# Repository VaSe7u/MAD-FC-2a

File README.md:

**MAD-FC-2a** quadrocopter flight controller.

This is a project of a flight controller for quadcopter. The [main source file][cpp] is designed to be descriptive of a multirotor flight controller algorithm. It is a concrete implementation that uses ATmega328P, MPU9255 and nRF24L01+ hardware but they can be easily replaced. The schematic and board layout for the flight controller and the remote board can be found in their respective circuit folders. The project depends on [MAD][madLink] library which is a common library for the flight controller and the remote.

*Not tested, Old project: [FC-alpha2][fcAlpha2].*

Flight Controller
=================
Schematic:
----------

Board:
----------

.jpg)

Photo:
----------

Remote
======
Schematic:
----------

Board:
----------

License
=======
The MIT License (MIT)

Copyright (c) 2016 Vasil Kalchev

Permission is hereby granted, free of charge, to any person obtaining a copy
of this software and associated documentation files (the "Software"), to deal
in the Software without restriction, including without limitation the rights
to use, copy, modify, merge, publish, distribute, sublicense, and/or sell
copies of the Software, and to permit persons to whom the Software is
furnished to do so, subject to the following conditions:

The above copyright notice and this permission notice shall be included in all
copies or substantial portions of the Software.

THE SOFTWARE IS PROVIDED "AS IS", WITHOUT WARRANTY OF ANY KIND, EXPRESS OR
IMPLIED, INCLUDING BUT NOT LIMITED TO THE WARRANTIES OF MERCHANTABILITY,
FITNESS FOR A PARTICULAR PURPOSE AND NONINFRINGEMENT. IN NO EVENT SHALL THE
AUTHORS OR COPYRIGHT HOLDERS BE LIABLE FOR ANY CLAIM, DAMAGES OR OTHER
LIABILITY, WHETHER IN AN ACTION OF CONTRACT, TORT OR OTHERWISE, ARISING FROM,
OUT OF OR IN CONNECTION WITH THE SOFTWARE OR THE USE OR OTHER DEALINGS IN THE
SOFTWARE.

[cpp]: https://github.com/VaSe7u/MAD-FC-2a/blob/master/code/MAD-FC-2a.ino
[madLink]: https://github.com/VaSe7u/MAD
[fcAlpha2]: https://github.com/VaSe7u/FC-alpha2

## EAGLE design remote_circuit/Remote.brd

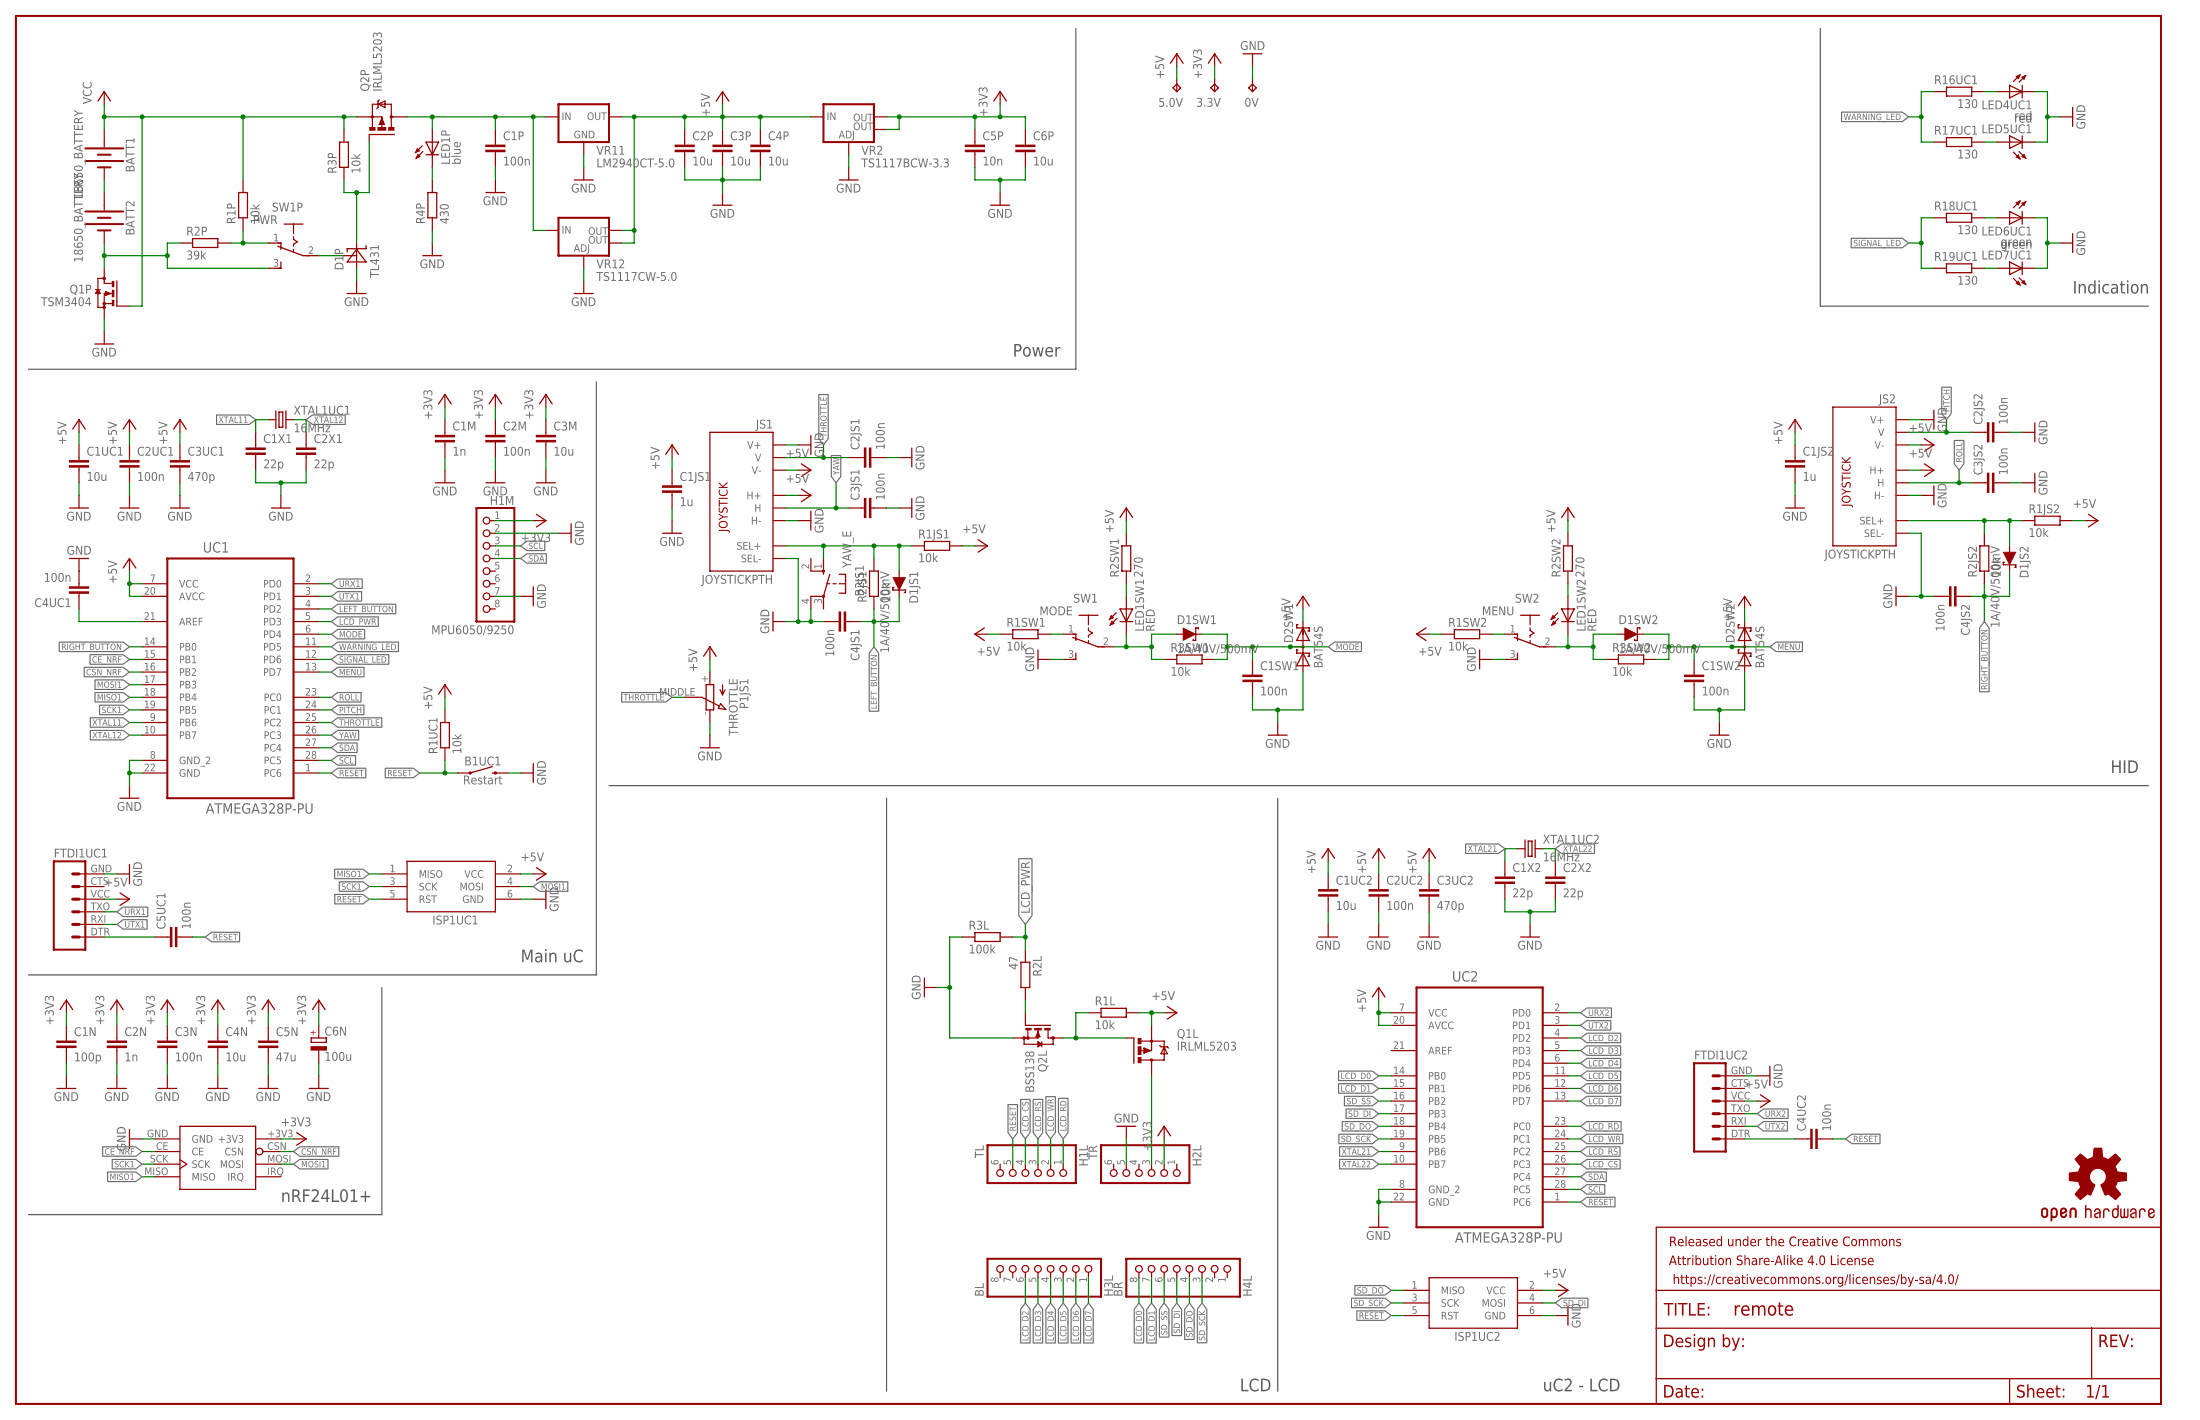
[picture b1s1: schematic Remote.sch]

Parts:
0V, 3.3V, 5.0V: TPTP10SQ; TP10SQ
B1: nRF24L01+; NRF24L01+_PA_LNA
B1UC1: Restart; TACTILE_SWITCH_SMD_6.0X3.5MM
B2JS1: YAW_E; B3F-40XX
BATT1, BATT2: 18650_BATTERY; BATTERY_HOLDER_18650
C1JS1, C1JS2: 1u; C1206
C1M, C2N: 1n; C1206
C1N: 100p; C1206
C1P, C1SW1, C1SW2, C2JS1, C2JS2, C2M, C2UC1, C2UC2, C3JS1, C3JS2, C3N, C4JS1, C4JS2, C4UC1, C4UC2, C5UC1: 100n; C1206
C1UC1, C1UC2, C2P, C3M, C3P, C4N, C4P, C6P: 10u; C1206
C1X1, C1X2, C2X1, C2X2: 22p; C1206
C3UC1, C3UC2: 470p; C1206
C5N: 47u; C3225
C5P: 10n; C1206
C6N: 100u; 153CLV-0505
D1JS1, D1JS2, D1SW1, D1SW2: 1A/40V/500mV; SMA-DIODE
D1P: TL431; SO-8
D2SW1, D2SW2: BAT54S; SOT23
FRAME2: FRAME-LEDGER; CREATIVE_COMMONS
FTDI1UC1, FTDI1UC2: FTDI_BASICPTH; FTDI_BASIC
H1L: TL; 1X06
H1M: MPU6050/9250; 1X08
H2L: TR; 1X06
H3L: BL; 1X08
H4L: BR; 1X08
ISP1UC1, ISP1UC2: AVRISP-6; AVRISP
JS1, JS2: JOYSTICKPTH; JOYSTICK
LED1P: blue; SML1206
LED1SW1, LED1SW2: RED; SML1206
LED4UC1: red; SML1206
LED5UC1: red; 1206
LED6UC1: green; SML1206
LED7UC1: green; 1206
LOGO1: OSHW-LOGOL-COPPER; OSHW-LOGO-L_COPPER
P1JS1: THROTTLE; SLIDE_POTENTIOMETER
Q1L, Q2P: IRLML5203; MICRO3
Q1P: TSM3404; SOT23
Q2L: BSS138; SOT23
R1JS1, R1JS2, R1L, R1P, R1SW1, R1SW2, R1UC1, R2JS1, R2JS2, R3P, R3SW1, R3SW2: 10k; R1206
R2L: 47; R1206
R2P: 39k; R1206
R2SW1, R2SW2: 270; R1206
R3L: 100k; R1206
R4P: 430; R1206
R16UC1, R17UC1, R18UC1, R19UC1: 130; R1206
SW1: MODE; SWITCH_2MM
SW1P: PWR; SWITCH_2MM
SW2: MENU; SWITCH_2MM
UC1, UC2: ATMEGA328P-PU; DIP254P762X457-28
VR2: TS1117BCW-3.3; SOT223
VR11: LM2940CT-5.0; 78XXL
VR12: TS1117CW-5.0; SOT223
XTAL1UC1, XTAL1UC2: 16MHz; HC49/S

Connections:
+3V3: 3.3V.TP, B1.+3V3, C1M.1, C1N.1, C2M.1, C2N.1, C3M.1, C3N.1, C4N.1, C5N.1, C5P.1, C6N.+, C6P.1, H1M.1, H2L.2, VR2.2 (OUT), VR2.4 (OUT)
+5V: 5.0V.TP, C1JS1.1, C1JS2.1, C1UC1.1, C1UC2.1, C2P.1, C2UC1.1, C2UC2.1, C3P.1, C3UC1.1, C3UC2.1, C4P.1, D2SW1.2 (C2), D2SW2.2 (C2), FTDI1UC1.VCC (4), FTDI1UC2.VCC (4), ISP1UC1.2 (VCC), ISP1UC2.2 (VCC), JS1.H1 (H+), JS1.V3 (V-), JS2.H1 (H+), JS2.V3 (V-), P1JS1.+, Q1L.2 (S), R1JS1.2, R1JS2.2, R1L.2, R1SW1.1, R1SW2.1, R1UC1.2, R2SW1.2, R2SW2.2, UC1.7 (VCC), UC1.20 (AVCC), UC2.7 (VCC), UC2.20 (AVCC), VR2.3 (IN), VR11.OUT, VR12.2 (OUT), VR12.4 (OUT)
CE_NRF: B1.CE, UC1.15 (PB1)
CSN_NRF: B1.CSN, UC1.16 (PB2)
GND: 0V.TP, B1.GND, B1UC1.2, B2JS1.4 (P1), C1JS1.2, C1JS2.2, C1M.2, C1N.2, C1P.2, C1SW1.2, C1SW2.2, C1UC1.2, C1UC2.2, C1X1.2, C1X2.2, C2JS1.2, C2JS2.2, C2M.2, C2N.2, C2P.2, C2UC1.2, C2UC2.2, C2X1.2, C2X2.2, C3JS1.2, C3JS2.2, C3M.2, C3N.2, C3P.2, C3UC1.2, C3UC2.2, C4JS1.2, C4JS2.2, C4N.2, C4P.2, C4UC1.2, C5N.2, C5P.2, C6N.-, C6P.2, D1P.2 (ANODE), D1P.3 (ANODE), D1P.6 (ANODE), D1P.7 (ANODE), D2SW1.1 (A1), D2SW2.1 (A1), FTDI1UC1.GND (6), FTDI1UC2.GND (6), H1M.2, H1M.7, H2L.5, ISP1UC1.6 (GND), ISP1UC2.6 (GND), JS1.B2A (SEL-), JS1.H3 (H-), JS1.V1 (V+), JS2.B2A (SEL-), JS2.H3 (H-), JS2.V1 (V+), LED4UC1.C, LED5UC1.C, LED6UC1.C, LED7UC1.C, P1JS1.-, Q1P.2 (S), Q2L.2 (S), R3L.1, R4P.1, SW1.3, SW2.3, UC1.8 (GND_2), UC1.22 (GND), UC2.8 (GND_2), UC2.22 (GND), VR2.1 (ADJ), VR11.GND, VR12.1 (ADJ)
LCD_CS: H1L.4, UC2.26 (PC3)
LCD_D0: H4L.8, UC2.14 (PB0)
LCD_D1: H4L.7, UC2.15 (PB1)
LCD_D2: H3L.6, UC2.4 (PD2)
LCD_D3: H3L.5, UC2.5 (PD3)
LCD_D4: H3L.4, UC2.6 (PD4)
LCD_D5: H3L.3, UC2.11 (PD5)
LCD_D6: H3L.2, UC2.12 (PD6)
LCD_D7: H3L.1, UC2.13 (PD7)
LCD_PWR: R2L.1, R3L.2, UC1.5 (PD3)
LCD_RD: H1L.1, UC2.23 (PC0)
LCD_RS: H1L.3, UC2.25 (PC2)
LCD_WR: H1L.2, UC2.24 (PC1)
LEFT_BUTTON: C4JS1.1, D1JS1.C, R2JS1.1, UC1.4 (PD2)
MENU: C1SW2.1, D1SW2.C, D2SW2.3 (C1A2), R3SW2.2, UC1.13 (PD7)
MISO1: B1.MISO, ISP1UC1.1 (MISO), UC1.18 (PB4)
MODE: C1SW1.1, D1SW1.C, D2SW1.3 (C1A2), R3SW1.2, UC1.6 (PD4)
MOSI1: B1.MOSI, ISP1UC1.4 (MOSI), UC1.17 (PB3)
unnamed: C4UC1.1, UC1.21 (AREF)
unnamed: LED1SW1.A, R2SW1.1
unnamed: C5UC1.1, FTDI1UC1.DTR (1)
unnamed: BATT1.-, BATT2.+
unnamed: R1SW2.2, SW2.1
unnamed: D1SW2.A, LED1SW2.C, R3SW2.1, SW2.2
unnamed: LED1P.C, R4P.2
unnamed: D1SW1.A, LED1SW1.C, R3SW1.1, SW1.2
unnamed: LED1SW2.A, R2SW2.1
unnamed: R1SW1.2, SW1.1
unnamed: D1JS2.A, JS2.B1A (SEL+), R1JS2.1, R2JS2.2
unnamed: BATT2.-, Q1P.3 (D), R2P.1, SW1P.3
unnamed: LED4UC1.A, R16UC1.1
unnamed: LED6UC1.A, R18UC1.1
unnamed: C4UC2.1, FTDI1UC2.DTR (1)
unnamed: LED5UC1.A, R17UC1.1
unnamed: H2L.3, Q1L.3 (D)
unnamed: LED7UC1.A, R19UC1.1
unnamed: C1P.1, LED1P.A, Q2P.3 (D), VR11.IN, VR12.3 (IN)
unnamed: D1P.8 (REFERENCE), SW1P.2
unnamed: R1P.1, R2P.2, SW1P.1
unnamed: Q1L.1 (G), Q2L.3 (D), R1L.1
unnamed: D1P.1 (CATHODE), Q2P.1 (G), R3P.1
unnamed: Q2L.1 (G), R2L.2
PITCH: C2JS2.1, JS2.V2 (V), UC1.24 (PC1)
RESET: B1UC1.1, C4UC2.2, C5UC1.2, H1L.5, ISP1UC1.5 (RST), ISP1UC2.5 (RST), R1UC1.1, UC1.1 (PC6), UC2.1 (PC6)
RIGHT_BUTTON: C4JS2.1, D1JS2.C, R2JS2.1, UC1.14 (PB0)
ROLL: C3JS2.1, JS2.H2 (H), UC1.23 (PC0)
SCK1: B1.SCK, ISP1UC1.3 (SCK), UC1.19 (PB5)
SCL: H1M.3, UC1.28 (PC5), UC2.28 (PC5)
SDA: H1M.4, UC1.27 (PC4), UC2.27 (PC4)
SD_DI: H4L.5, ISP1UC2.4 (MOSI), UC2.17 (PB3)
SD_DO: H4L.4, ISP1UC2.1 (MISO), UC2.18 (PB4)
SD_SCK: H4L.3, ISP1UC2.3 (SCK), UC2.19 (PB5)
SD_SS: H4L.6, UC2.16 (PB2)
SIGNAL_LED: R18UC1.2, R19UC1.2, UC1.12 (PD6)
SN1: B2JS1.1 (S), D1JS1.A, JS1.B1A (SEL+), R1JS1.1, R2JS1.2
THROTTLE: C2JS1.1, JS1.V2 (V), P1JS1.MIDDLE, UC1.25 (PC2)
URX1: FTDI1UC1.TXO (3), UC1.2 (PD0)
URX2: FTDI1UC2.TXO (3), UC2.2 (PD0)
UTX1: FTDI1UC1.RXI (2), UC1.3 (PD1)
UTX2: FTDI1UC2.RXI (2), UC2.3 (PD1)
VCC: BATT1.+, Q1P.1 (G), Q2P.2 (S), R1P.2, R3P.2
WARNING_LED: R16UC1.2, R17UC1.2, UC1.11 (PD5)
XTAL11: C1X1.1, UC1.9 (PB6), XTAL1UC1.1
XTAL12: C2X1.1, UC1.10 (PB7), XTAL1UC1.2
XTAL21: C1X2.1, UC2.9 (PB6), XTAL1UC2.1
XTAL22: C2X2.1, UC2.10 (PB7), XTAL1UC2.2
YAW: C3JS1.1, JS1.H2 (H), UC1.26 (PC3)

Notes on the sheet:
Power
nRF24L01+
LCD
uC2 - LCD
HID
Indication
Main uC

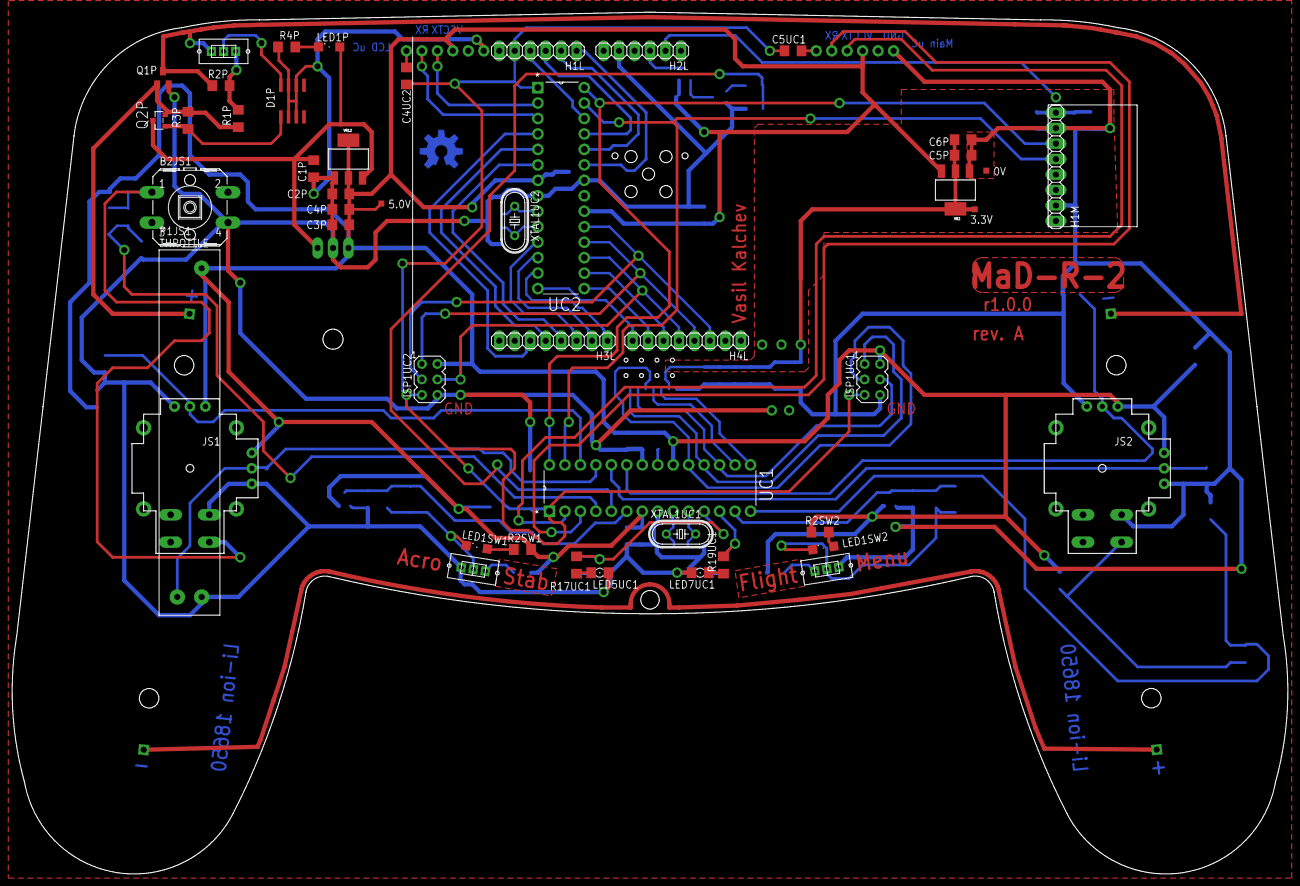
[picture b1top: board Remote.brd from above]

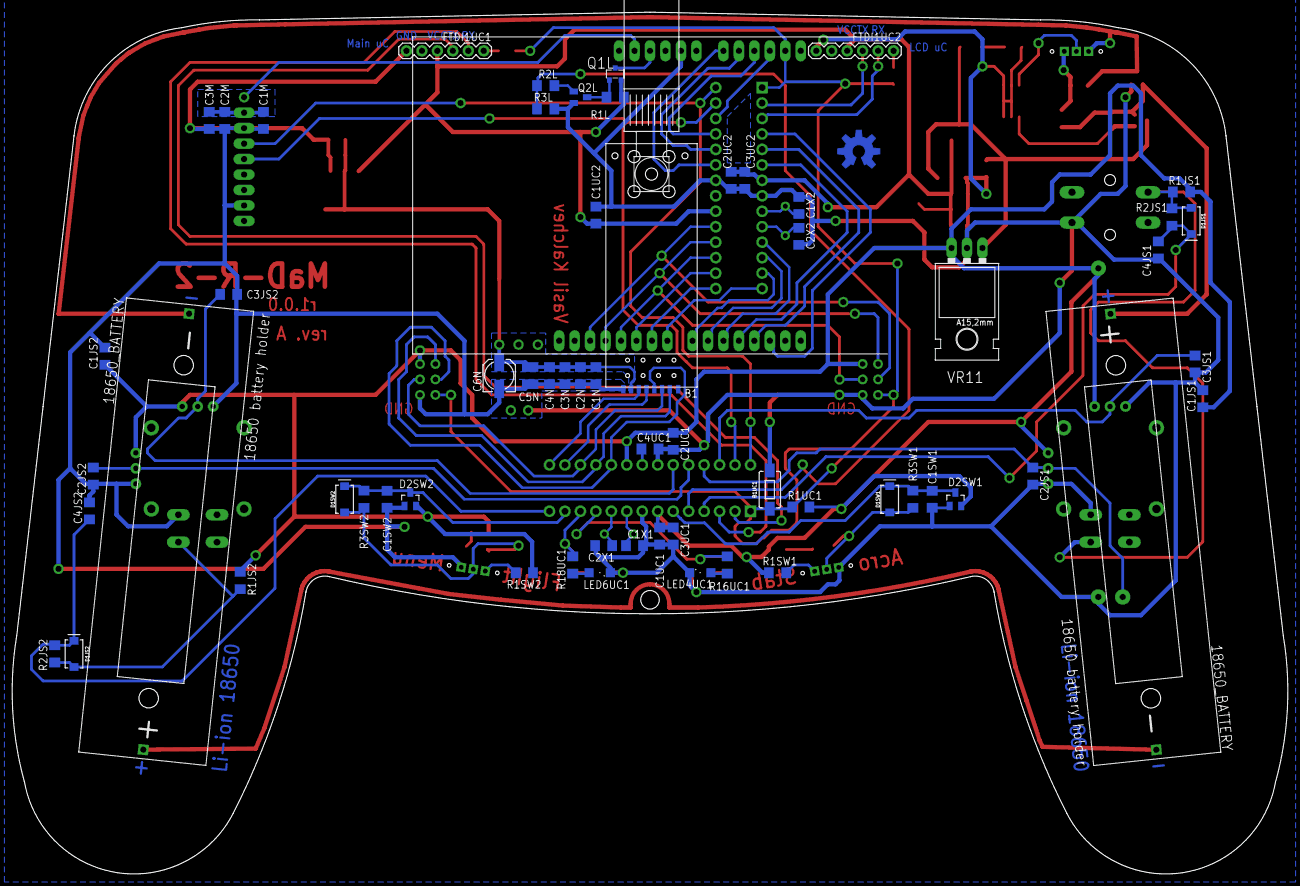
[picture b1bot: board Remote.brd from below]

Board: 2 copper layers, 209.5 x 141.5 mm, 110 parts (62 on the bottom side), 72 nets.

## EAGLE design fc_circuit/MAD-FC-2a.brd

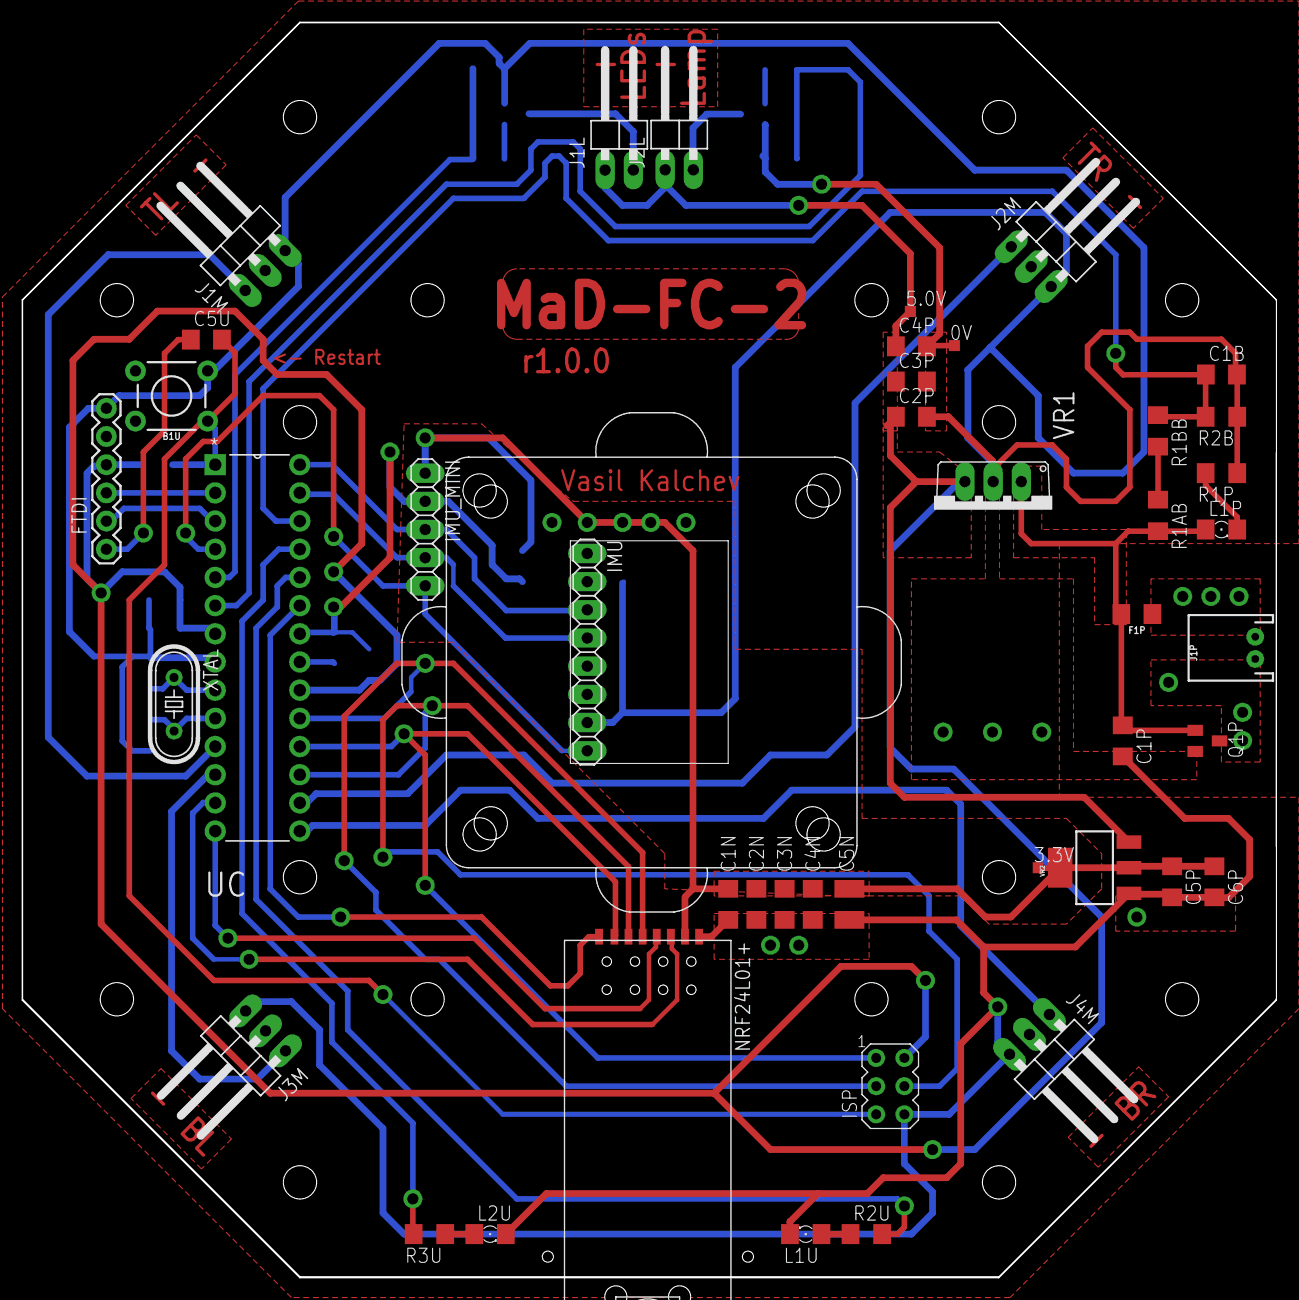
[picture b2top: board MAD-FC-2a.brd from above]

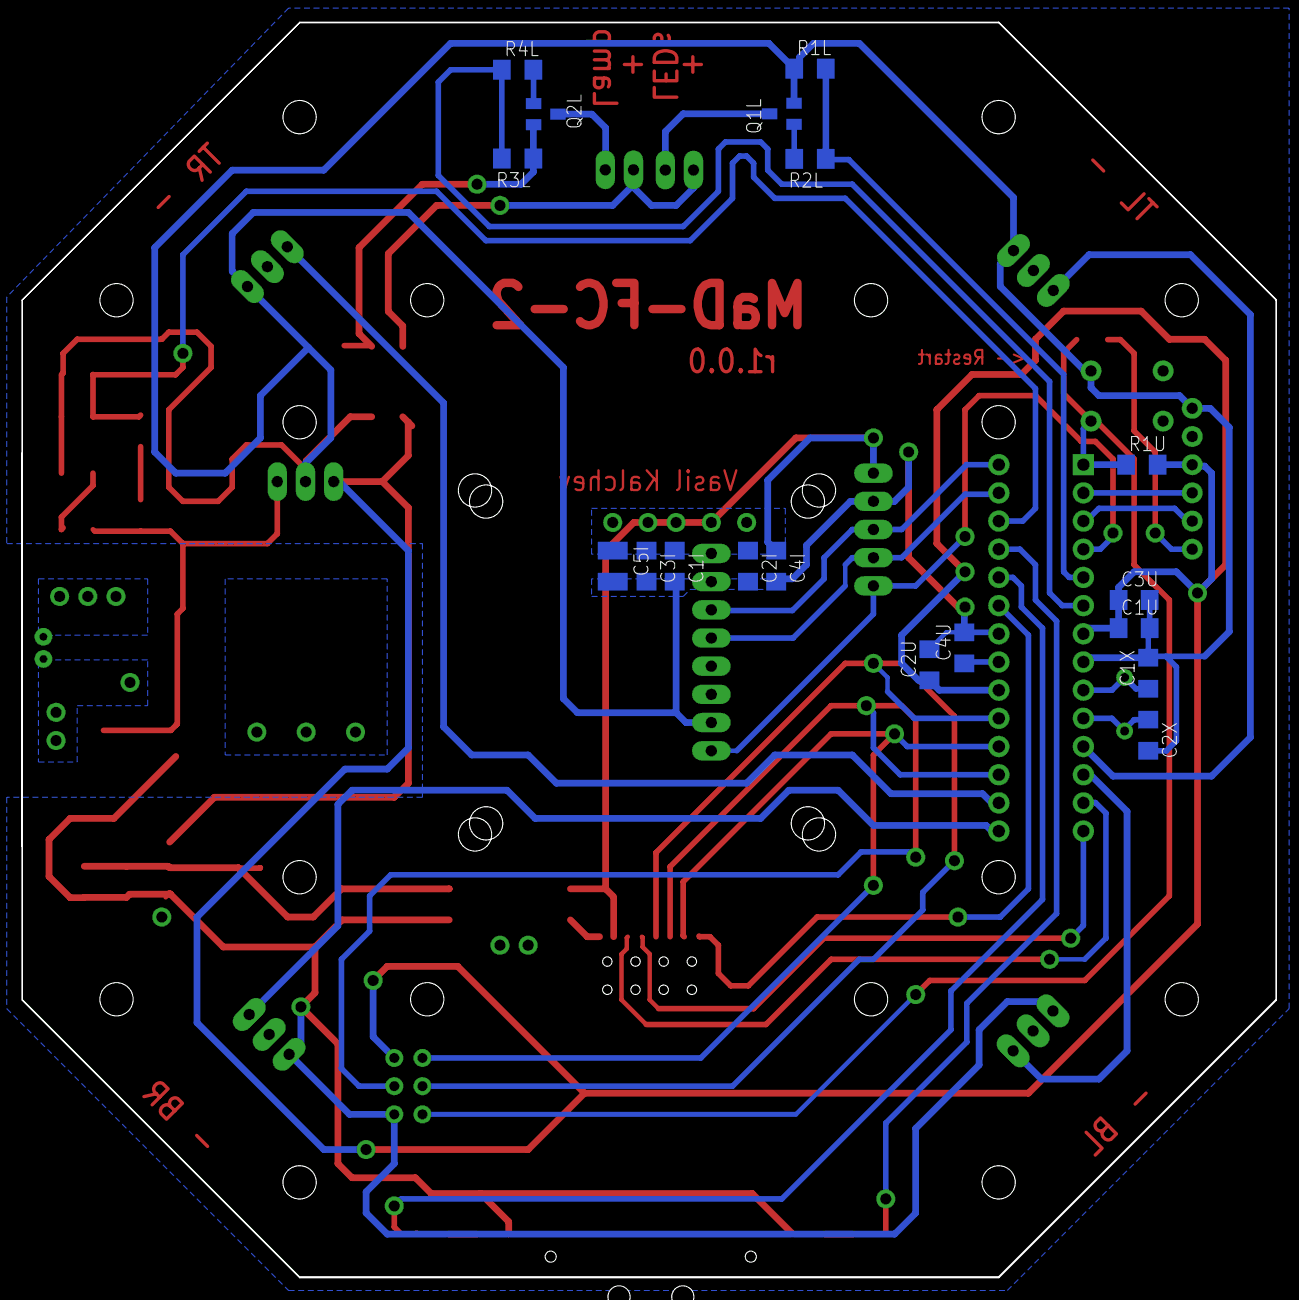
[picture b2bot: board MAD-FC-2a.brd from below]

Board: 2 copper layers, 113.0 x 113.2 mm, 64 parts (18 on the bottom side), 39 nets.

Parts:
0V, 3.3V, 5.0V: TPTP10SQ; TP10SQ
B1U: Restart; TACTILE_SWITCH_PTH_6.0MM
C1B, C1U, C2P, C3P, C4I, C4N, C4P, C6P: 10u; C1206
C1I, C1N: 100p; C1206
C1P, C2U, C3I, C3N, C4U, C5U: 100n; C1206
C1X, C2X: 22p; C1206
C2I, C2N: 1n; C1206
C3U: 470p; C1206
C5I, C5N: 100u_6.3x5.3; C3225
C5P: 10n; C1206
F1P: 2A; 1206
FTDI: FTDI_BASIC
IMU: MPU6050/9250; 1X08
IMU_MINI: MPU6050/9250; 1X05
ISP: AVRISP-6; AVRISP
J1L, J2L: 1X02/90
J1M: TL; 1X03/90
J1P: LiPo; JST-2-PTH
J2M: TR; 1X03/90
J3M: BL; 1X03/90
J4M: BR; 1X03/90
L1P: blue; 1206
L1U: red; 1206
L2U: green; 1206
NRF24L01+: nRF24L01+; NRF24L01+_PA_LNA_SMD
Q1L, Q1P, Q2L: TSM3404; SOT23
R1AB: 110k; R1206
R1BB: 20k; R1206
R1L, R3L: 100k; R1206
R1P: 680; R1206
R1U: 10k; R1206
R2B: 9k1; R1206
R2L, R4L: 33; R1206
R2U, R3U: 130; R1206
U$2: F450_TOP_PLATE
U$3: ANTI-VIBRATION_PLATE
UC: ATMEGA328P-PU; DIP254P762X457-28
VR1: 7805; TO220V
VR2: TS1117BCW-3.3; SOT223
XTAL: 16MHz; HC49/S

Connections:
+3V3: 3.3V.TP, C1I.1, C1N.1, C2I.1, C2N.1, C3I.1, C3N.1, C4I.1, C4N.1, C5I.1, C5N.1, C5P.1, C6P.1, IMU.1, IMU_MINI.1, NRF24L01+.+3V3, VR2.2, VR2.4
+5V: 5.0V.TP, C1U.1, C2P.1, C2U.1, C3P.1, C3U.1, C4P.1, FTDI.VCC, ISP.2, J1L.1, J2L.1, R1U.2, UC.7, UC.20, VR1.3, VR2.3
BATTERY_VOLTAGE: C1B.1, R1BB.1, R2B.2, UC.26
BL: J3M.1, UC.12
BR: J4M.1, UC.15
CE_NRF: NRF24L01+.CE, UC.13
CSN_NRF: NRF24L01+.CSN, UC.14
GND: 0V.TP, B1U.3, C1B.2, C1I.2, C1N.2, C1P.2, C1U.2, C1X.2, C2I.2, C2N.2, C2P.2, C2U.2, C2X.2, C3I.2, C3N.2, C3P.2, C3U.2, C4I.2, C4N.2, C4P.2, C4U.2, C5I.2, C5N.2, C5P.2, C6P.2, FTDI.GND, IMU.2, IMU.7, IMU_MINI.2, ISP.6, J1M.3, J2M.3, J3M.3, J4M.3, L1U.C, L2U.C, NRF24L01+.GND, Q1L.2, Q1P.2, Q2L.2, R1L.1, R1P.1, R2B.1, R3L.1, UC.8, UC.22, VR1.2, VR2.1
GND-ISO: J1P.1, Q1P.3
INT_IMU: IMU.8, IMU_MINI.5, UC.4
INT_NRF: NRF24L01+.IRQ, UC.23
LAMP_CONTROL: R3L.2, R4L.1, UC.6
LAMP_SINK: J2L.2, Q2L.3
LEDS_CONTROL: R1L.2, R2L.1, UC.5
LEDS_SINK: J1L.2, Q1L.3
MISO: ISP.1, NRF24L01+.MISO, UC.18
MOSI: ISP.4, NRF24L01+.MOSI, UC.17
unnamed: L2U.A, R3U.1
unnamed: R1AB.1, R1BB.2
unnamed: L1U.A, R2U.1
unnamed: Q1L.1, R2L.2
unnamed: Q2L.1, R4L.2
unnamed: L1P.C, R1P.2
unnamed: C4U.1, UC.21
unnamed: C5U.1, FTDI.DTR
RESET: B1U.1, C5U.2, ISP.5, R1U.1, UC.1
SCK: ISP.3, NRF24L01+.SCK, UC.19
SCL: IMU.3, IMU_MINI.3, UC.28
SDA: IMU.4, IMU_MINI.4, UC.27
SIGNAL_LED: R3U.2, UC.25
TL: J1M.1, UC.11
TR: J2M.1, UC.16
URX: FTDI.TXO, UC.2
UTX: FTDI.RXI, UC.3
VCC-ISO: F1P.1, J1P.2
V_BATT: C1P.1, F1P.2, L1P.A, Q1P.1, R1AB.2, VR1.1
WARNING_LED: R2U.2, UC.24
XTAL1: C1X.1, UC.9, XTAL.1
XTAL2: C2X.1, UC.10, XTAL.2

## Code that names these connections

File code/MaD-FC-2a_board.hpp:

#pragma once
#include <stdint.h>
#include <avr/io.h>

const uint32_t F_CPU = 16000000;

using namespace m328;

uint32_t us();
// float ms();


namespace board {

namespace pin {
namespace motor {
const uint8_t tl = PD5;
const uint8_t tr = PB2;
const uint8_t bl = PD6;
const uint8_t br = PB1;
} //namespace motor
namespace indication {
const uint8_t arms = PD3;
const uint8_t lamp = PD4;
const uint8_t signal = PC2;
const uint8_t warning = PC1;
} //namespace indication
namespace input {
namespace imu {
const uint8_t interrupt = PD2;
} //namespace imu
const uint8_t batteryVoltage = PC3;
} //namespace input
namespace communication {
const uint8_t ce = PD7;
const uint8_t csn = PB0;
const uint8_t interrupt = PC0;
} //namespace communication

// namespace ino {
// namespace motor {
// const uint8_t tl = 5;
// const uint8_t tr = 10;
// const uint8_t bl = 6;
// const uint8_t br = 9;
// } //namespace motor
// namespace indication {
// const uint8_t arms = 3;
// const uint8_t lamp = 4;
// const uint8_t signal = A2;
// const uint8_t warning = A1;
// } //namespace indication
// namespace input {
// namespace imu {
// const uint8_t interrupt = 2;
// } //namespace imu
// const uint8_t batteryVoltage = A3;
// } //namespace input
// namespace communication {
// const uint8_t ce = 7;
// const uint8_t csn = 8;
// const uint8_t interrupt = A0;
// } //namespace communication
// } //namespace ino

} //namespace pin


namespace imu {
namespace mpu925x {
namespace offset {
namespace accelerometer {
NVP<int16_t> x(2587);
NVP<int16_t> y(-2483);
NVP<int16_t> z(5226);
} //namespace accelerometer
namespace gyroscope {
NVP<int16_t> x(4);
NVP<int16_t> y(-6);
NVP<int16_t> z(2);
} //namespace gyroscope
} //namespace offset
} //namespace mpu925x
} //namespace imu


void initializeIO() __attribute__ ((naked)) __attribute__ ((section (".init3")));
void initializeTimers() __attribute__ ((naked)) __attribute__ ((section (".init3")));
void disableTimer0OverflowInterrupt() __attribute__ ((naked)) __attribute__ ((section (".init3")));
void configureTimer2ForUs() __attribute__ ((naked)) __attribute__ ((section (".init3")));
void configureTimer0And1For490HzPhaseCorrectPwm() __attribute__ ((naked)) __attribute__ ((section (".init3")));


namespace motor {
void tl(const uint8_t pwm);
void tr(const uint8_t pwm);
void bl(const uint8_t pwm);
void br(const uint8_t pwm);
} //namespace motor

namespace indication {
const uint8_t armsLevel();
void arms(const uint8_t pwm);
void armsToggle();

const bool lampState();
void lamp(const bool state);
void lampToggle();

const bool signalState();
void signal(const bool state);
void signalToggle();

const bool warningState();
void warning(const bool state);
void warningToggle();
} //namespace indication

const float analogReference = 1.1;

namespace battery {
const float voltageDivider = 0.0654205607476635514018691588785; // R1 = 130kOhm, R2 = 9.1kOhm
// Battery voltage = analogRead() * (Analog Reference / (Analog Resolution * Voltage Divider))
constexpr float readingMultiplier = analogReference / (1024.0f * voltageDivider);
} //namespace battery

} //namespace board

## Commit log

2018-05-04 pics

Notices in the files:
parts and their libraries:
SparkFun-Fuses: Licensing: Creative Commons ShareAlike 4.0 International - https://creativecommons.org/licenses/by-sa/4.0
SparkFun-Aesthetics: Released under the Creative Commons Attribution Share-Alike 4.0 License
SparkFun-Aesthetics: https://creativecommons.org/licenses/by-sa/4.0
